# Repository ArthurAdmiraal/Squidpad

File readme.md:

# Squidpad
### About
The squidpad is a Slim Quality Uncostly Intuitive Drawing Pad. These are all the source files. This is an open project, which I'm documenting on [hackaday.io](https://hackaday.io/project/7153-squidpad).

### Repository structure
All design files go in the `Project` folder. Any files just made for documentation, such as a diagram in GeoGebra, can be found in the `Documentation` folder.

In both folders, the `Design files` folder contains source files. In the `Documentation` folder, any diagrams of pictures are just in the top-level folder. In the `Project` folder however, files generated using the design software, such as gerber files, can be found in the `Manifacturing` folder. People that just want to have a look at the board can find pdf's and OSHpark renders in the `Easily viewable` folder.

### License
All files in the `Project` folder are licensed under the [Creative Commons Attribution-NonCommercial-ShareAlike 4.0 International](http://creativecommons.org/licenses/by-nc-sa/4.0/) license. Everything in the `Documentation` folder can be used under the [Creative Commons Attribution-ShareAlike 4.0 International](http://creativecommons.org/licenses/by-sa/4.0/) license.

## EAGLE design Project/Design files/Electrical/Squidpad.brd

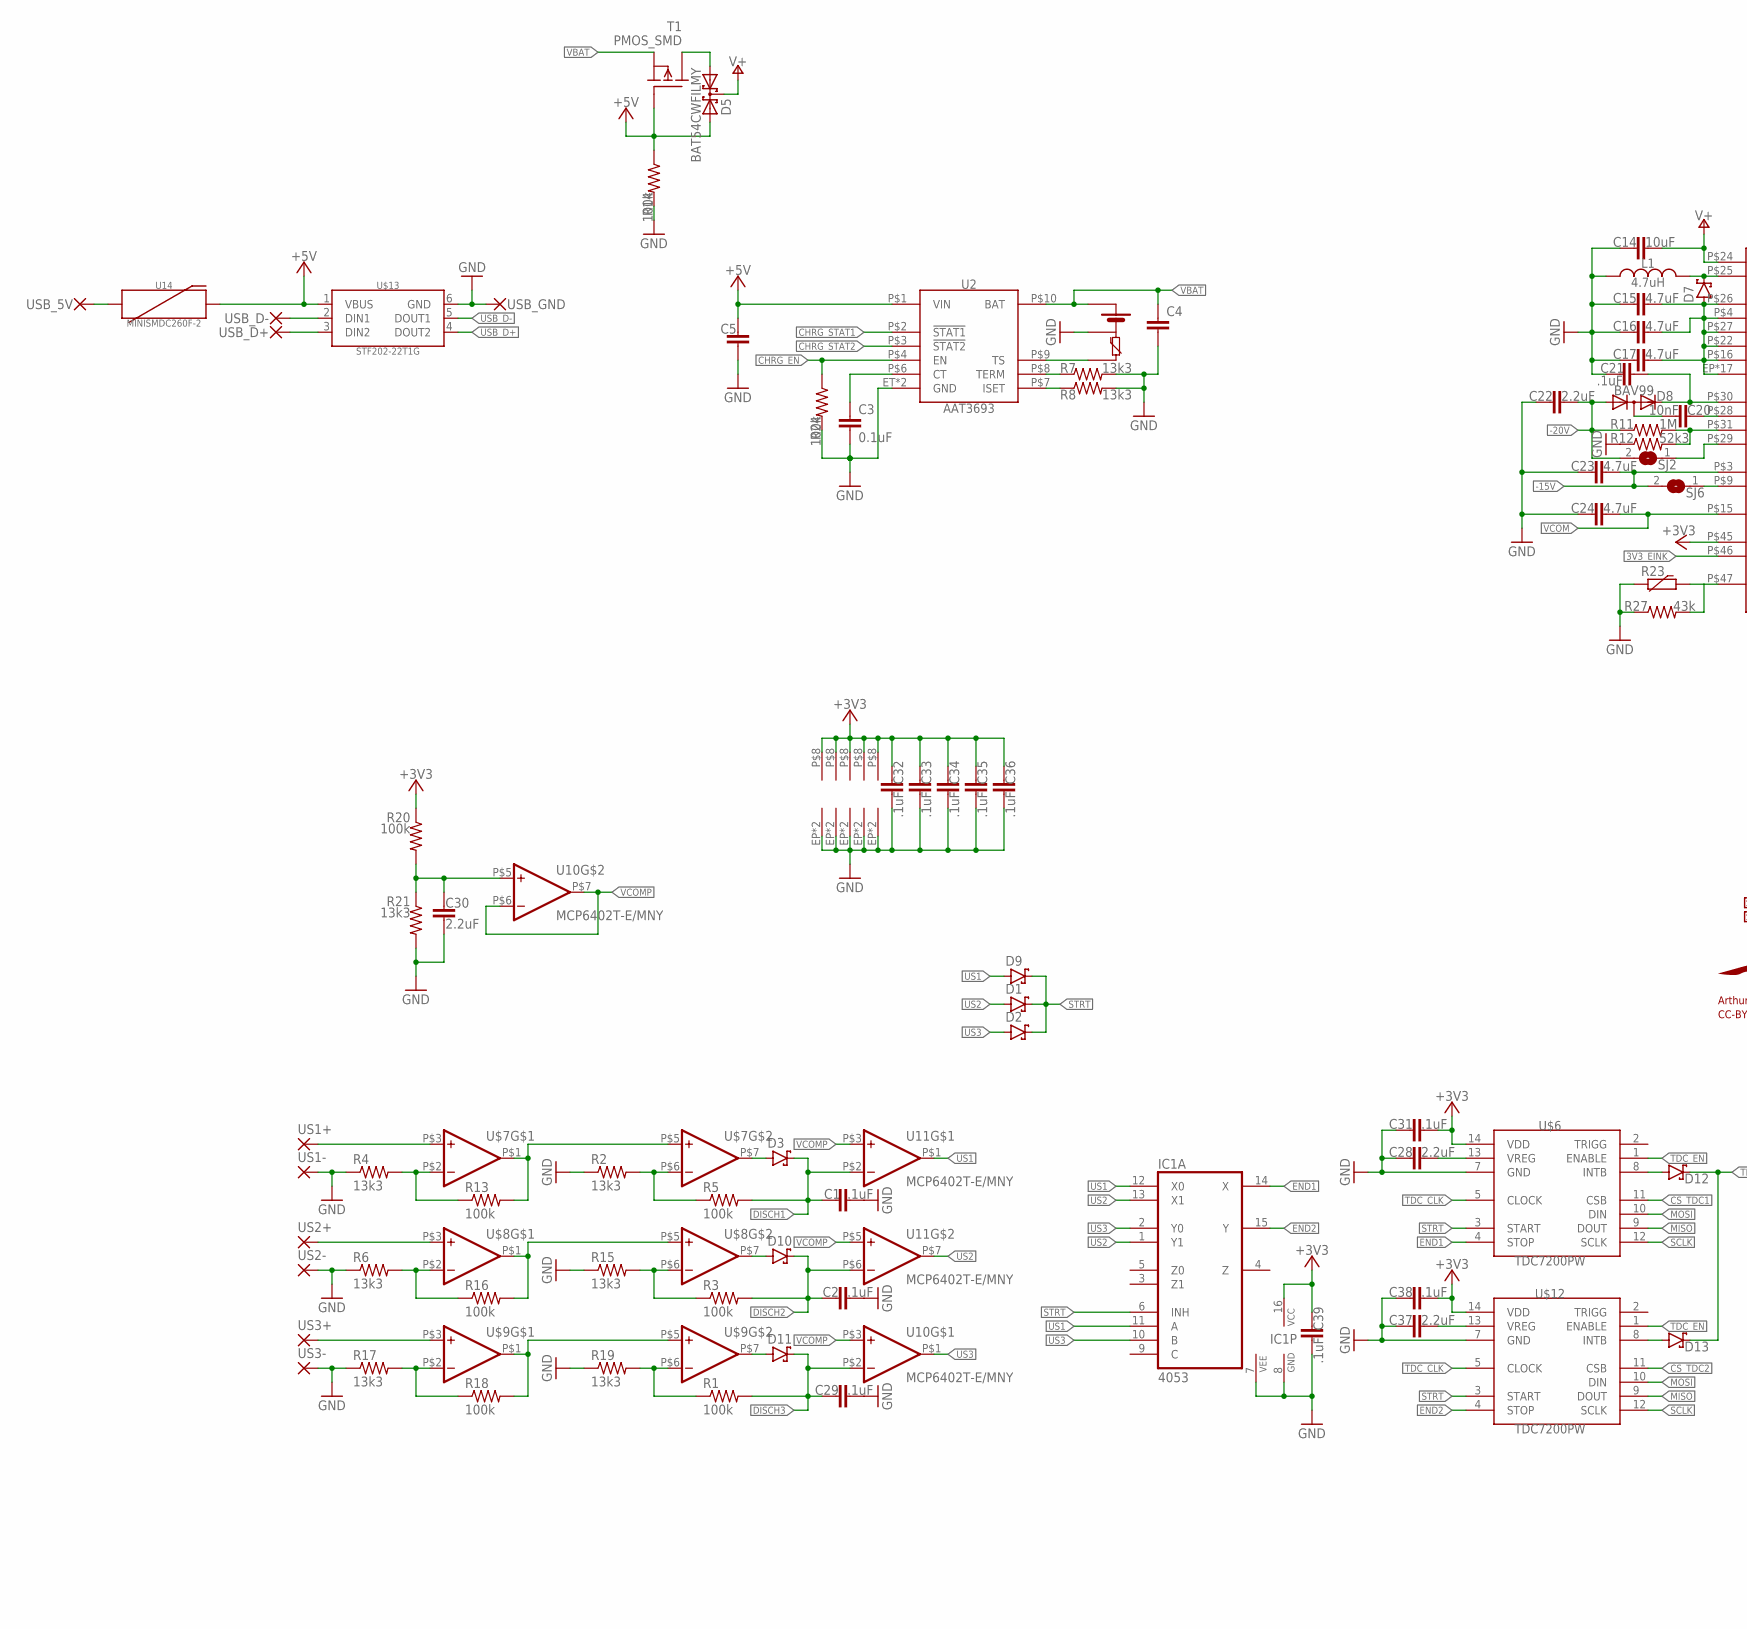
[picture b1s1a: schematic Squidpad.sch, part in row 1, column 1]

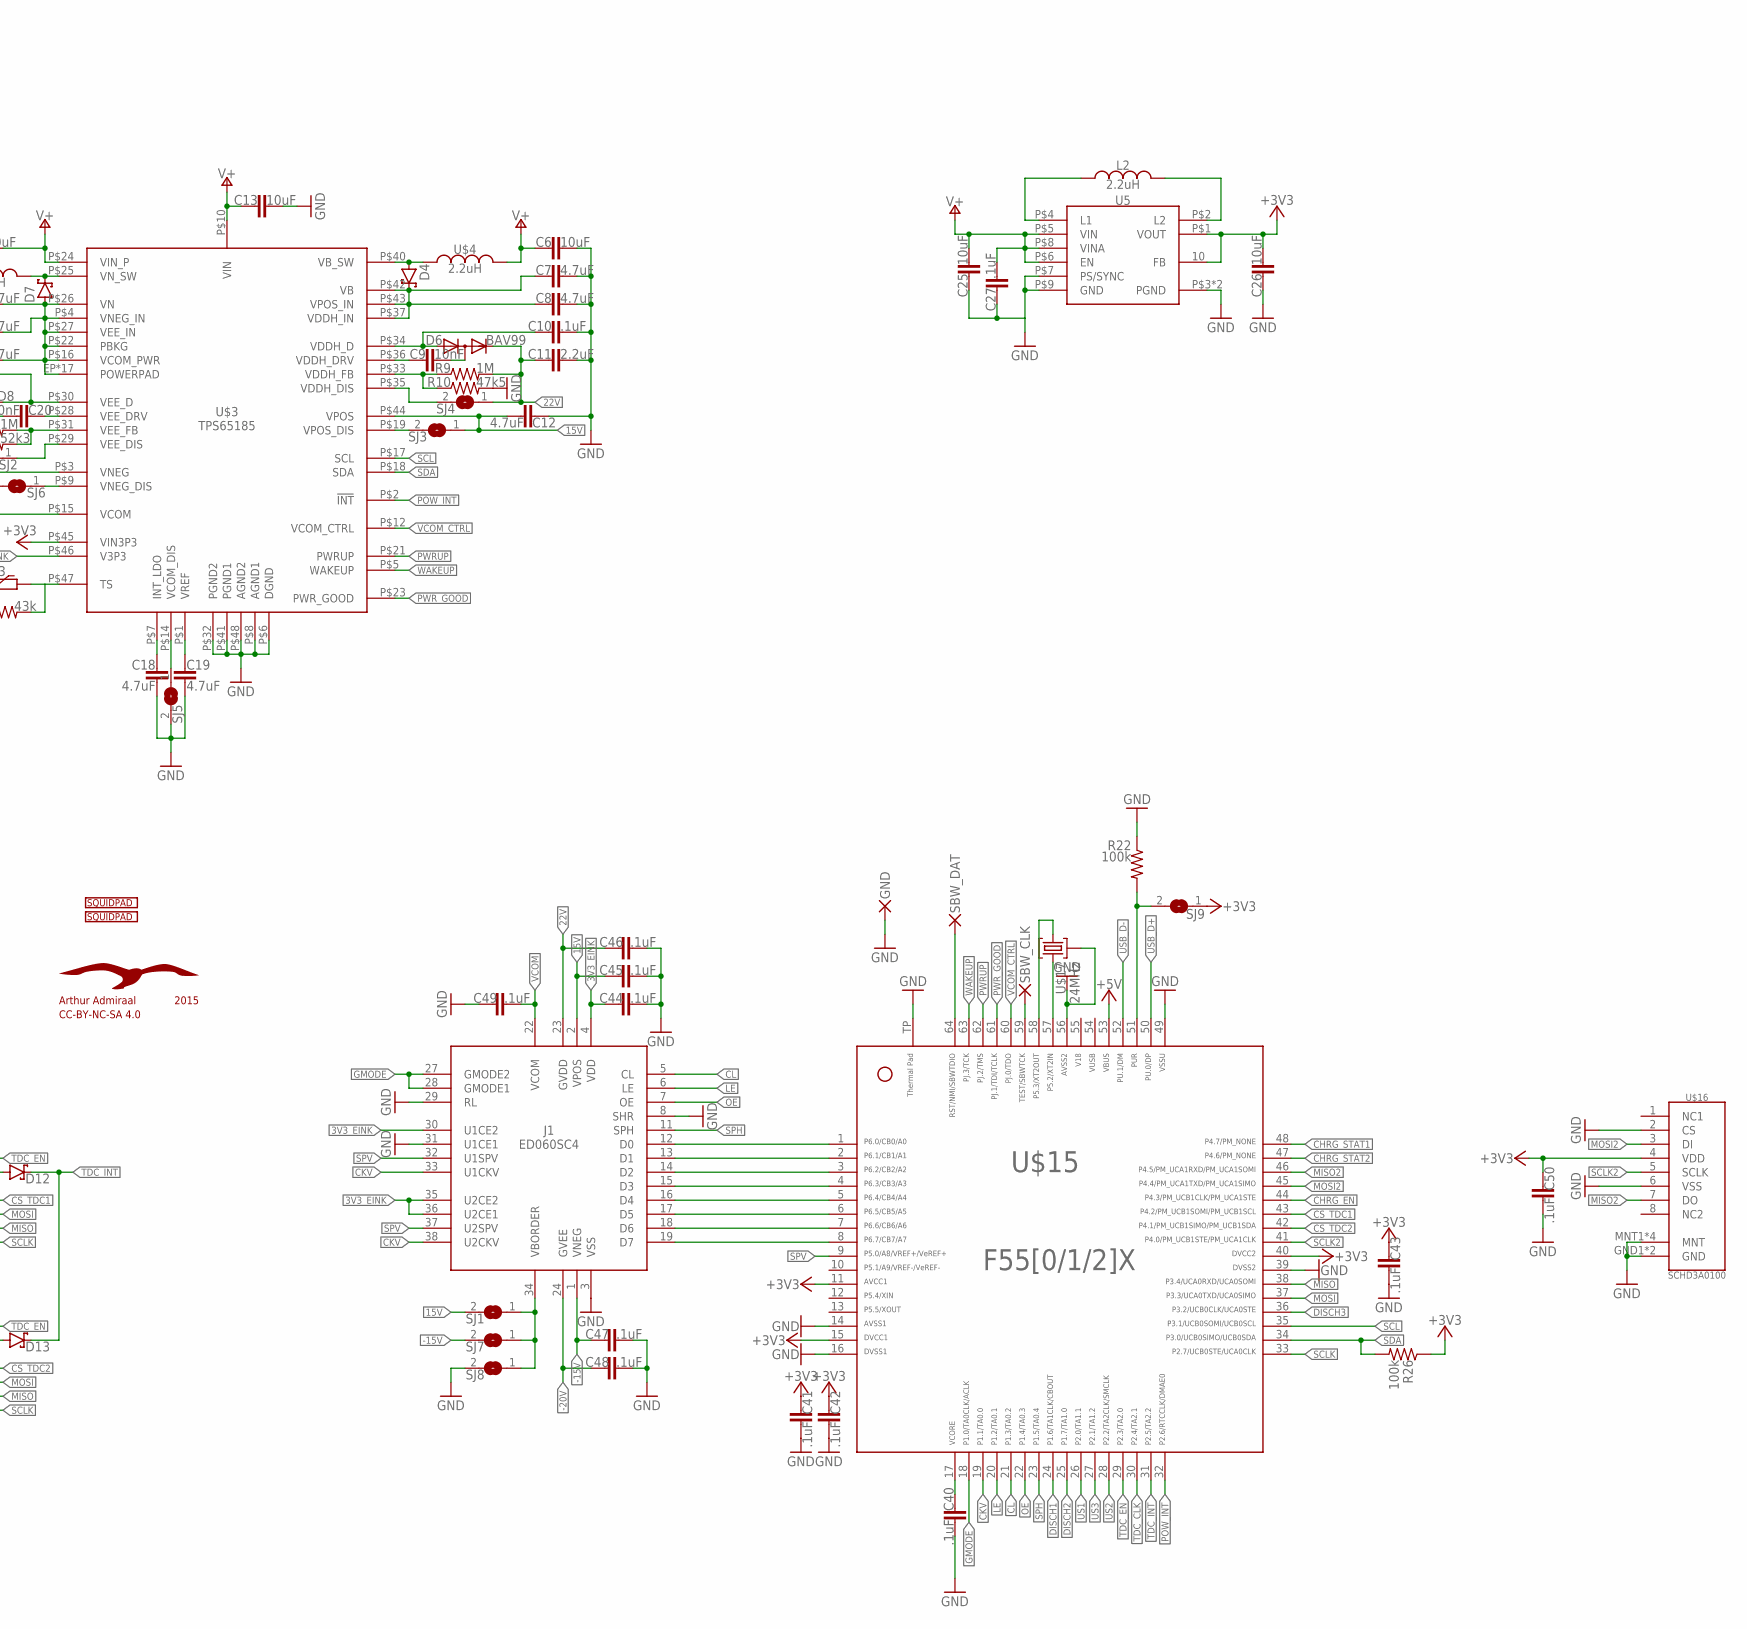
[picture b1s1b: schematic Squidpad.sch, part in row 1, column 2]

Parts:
C1, C2, C10, C21, C27, C29, C31, C32, C33, C34, C35, C36, C38, C39, C40, C41, C42, C43, C44, C45, C46, C47, C48, C49, C50: .1uF; C0805K
C3: 0.1uF; 0603-CAP
C4, C5: CAP0603-CAP; 0603-CAP
C6, C13, C14, C25, C26: 10uF; C0805K
C7, C8, C12, C15, C16, C17, C18, C19, C23, C24: 4.7uF; C0805K
C9, C20: 10nF; C0603K
C11, C22, C28, C30, C37: 2.2uF; C0603K
D1, D2, D3, D4, D7, D9, D10, D11, D12, D13: MBR130T3G; SOD123
D5: BAT54CWFILMY; SOT323
D6, D8: BAV99; SOT23
GND: SMD2; SMD1,27-2,54
IC1: 4053; TSSOP16
J1: ED060SC4; FH26-39S-0.3SHW(05)
L1: 4.7uH; LQH44P
L2: 2.2uH; NR4012
R1, R3, R5, R13, R14, R16, R18, R20, R22, R24, R26: 100k; R0603
R2, R4, R6, R15, R17, R19, R21: 13k3; R1206
R7, R8: 13k3; R0603
R9, R11: 1M; R0603
R10: 47k5; R0603
R12: 52k3; R0603
R23: R-EU_R0603; R0603
R27: 43k; R0603
SBW_CLK: SMD2; SMD1,27-2,54
SBW_DAT: SMD2; SMD1,27-2,54
SJ1, SJ2, SJ3, SJ4, SJ5, SJ6, SJ7, SJ8, SJ9: SJ
T1: PMOS_SMD; SOT323R_INFINEON
U2: AAT3693; TDFN14
U5: TPS63031; R-PWSON-N10
U10, U11: MCP6402T-E/MNY; TFDN8
U14: MINISMDC260F-2
U$1: IPOD_NANO_5_BATTERY
U$2: SQUIDPAD_LOGOSQUIDPAD_LOGO_SMALL; SQUIDPAD_LOGO_LOWPOLY_SMALL
U$3: TPS65185; VQFN48
U$4: 2.2uH; NR4012
U$5: SQUIDPAD_LOGOSQUIDPAD_LOGO; SQUIDPAD_LOGO_LOWPOLY
U$6, U$12: TDC7200PW; TSSOP14
U$7, U$8, U$9: MCP6402T-E/MNY; TFDN8
U$10: AALECTRONICS_SEAGULL
U$13: STF202-22T1G; SOT23-6
U$15: F55[0/1/2]X---RGC64; RGC64
U$16: SCHD3A0100
U$17: 24MHz; TSX-3225
US1+, US1-, US2+, US2-, US3+, US3-: SMD2; SMD1,27-2,54
USB_5V: SMD2; SMD1,27-2,54
USB_D+: SMD2; SMD1,27-2,54
USB_D-: SMD2; SMD1,27-2,54
USB_GND: SMD2; SMD1,27-2,54

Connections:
3V3: C6.1, C13.1, C14.2, C25.2, C27.2, D5.3 (C), U5.P$5 (VIN), U5.P$6 (EN), U5.P$8 (VINA), U$3.P$10 (VIN), U$3.P$24 (VIN_P), U$4.P$2
3V3_EINK: C44.1, J1.4 (VDD), J1.30 (U1CE2), J1.35 (U2CE2), J1.36 (U2CE1), U$3.P$46 (V3P3)
15V: C12.2, C45.1, J1.2 (VPOS), SJ1.2, SJ3.1, U$3.P$44 (VPOS)
22V: C11.1, C46.1, D6.2 (C), J1.23 (GVDD), R9.2, SJ4.1
54: U$15.54
55: U$15.55
+3V3: C26.2, C31.2, C32.1, C33.1, C34.1, C35.1, C36.1, C38.2, C39.1, C41.1, C42.1, C43.1, C50.1, IC1.16 (VCC), R20.1, R26.1, SJ9.1, U5.10 (FB), U5.P$1 (VOUT), U10.P$8 (V+), U11.P$8 (V+), U$3.P$45 (VIN3P3), U$6.14 (VDD), U$7.P$8 (V+), U$8.P$8 (V+), U$9.P$8 (V+), U$12.14 (VDD), U$15.11, U$15.15, U$15.40, U$16.4 (VDD)
+5V: C5.1, D5.2 (A2), R14.1, T1.1 (G), U2.P$1 (VIN), U14.P$2, U$13.1 (VBUS), U$15.53
-15V: C23.2, C47.1, J1.1 (VNEG), SJ6.2, SJ7.2, U$3.P$3 (VNEG)
-20V: C22.2, C48.1, D8.1 (A), J1.24 (GVEE), R11.1, SJ2.2
CHRG_EN: R24.1, U2.P$4 (EN), U$15.44
CHRG_STAT1: U2.P$2 (!STAT1), U$15.48
CHRG_STAT2: U2.P$3 (!STAT2), U$15.47
CKV: J1.33 (U1CKV), J1.38 (U2CKV), U$15.19
CL: J1.5 (CL), U$15.21
CS_TDC1: U$6.11 (CSB), U$15.43
CS_TDC2: U$12.11 (CSB), U$15.42
D0: J1.12 (D0), U$15.1
D1: J1.13 (D1), U$15.2
D2: J1.14 (D2), U$15.3
D3: J1.15 (D3), U$15.4
D4: J1.16 (D4), U$15.5
D5: J1.17 (D5), U$15.6
D6: J1.18 (D6), U$15.7
D7: J1.19 (D7), U$15.8
DISCH1: C1.1, D3.1 (C), R5.2, U11.P$2 (-IN), U$15.24
DISCH2: C2.1, D10.1 (C), R3.2, U11.P$6 (-IN), U$15.25
DISCH3: C29.1, D11.1 (C), R1.2, U10.P$2 (-IN), U$15.36
END1: IC1.14 (X), U$6.4 (STOP)
END2: IC1.15 (Y), U$12.4 (STOP)
GMODE: J1.27 (GMODE2), J1.28 (GMODE1), U$15.18
GND: C1.2, C2.2, C3.2, C4.2, C5.2, C6.2, C7.2, C8.2, C10.2, C11.2, C12.1, C13.2, C14.1, C15.1, C16.1, C17.1, C18.1, C19.1, C21.1, C22.1, C23.1, C24.1, C25.1, C26.1, C27.1, C28.1, C29.2, C30.2, C31.1, C32.2, C33.2, C34.2, C35.2, C36.2, C37.1, C38.1, C39.2, C40.2, C41.2, C42.2, C43.2, C44.2, C45.2, C46.2, C47.2, C48.2, C49.1, C50.2, GND.1, IC1.7 (VEE), IC1.8 (GND), J1.3 (VSS), J1.8 (SHR), J1.29 (RL), J1.31 (U1CE1), L1.P$1, R2.1, R4.1, R6.1, R7.2, R8.2, R10.2, R12.1, R14.2, R15.1, R17.1, R19.1, R21.2, R22.1, R23.1, R24.2, R27.1, SJ5.2, SJ8.2, U2.ET (GND), U2.P$5 (GND), U5.P$3 (PGND), U5.P$7 (PS/SYNC), U5.P$9 (GND), U5.POWERPAD (PGND), U10.EP (V-), U10.P$4 (V-), U11.EP (V-), U11.P$4 (V-), U$1.P- (BATTERY-), U$3.P$6 (DGND), U$3.P$8 (AGND1), U$3.P$32 (PGND2), U$3.P$41 (PGND1), U$3.P$48 (AGND2), U$6.7 (GND), U$7.EP (V-), U$7.P$4 (V-), U$8.EP (V-), U$8.P$4 (V-), U$9.EP (V-), U$9.P$4 (V-), U$12.7 (GND), U$13.6 (GND), U$15.14, U$15.16, U$15.39, U$15.49, U$15.56, U$15.TP, U$16.2 (CS), U$16.6 (VSS), U$16.GND1 (GND), U$16.GND2 (GND), U$16.MNT1 (MNT), U$16.MNT2 (MNT), U$16.MNT3 (MNT), U$16.MNT4 (MNT), U$17.2, U$17.3 (2), US1-.1, US2-.1, US3-.1, USB_GND.1
LE: J1.6 (LE), U$15.20
MISO: U$6.9 (DOUT), U$12.9 (DOUT), U$15.38
MISO2: U$15.46, U$16.7 (DO)
MOSI: U$6.10 (DIN), U$12.10 (DIN), U$15.37
MOSI2: U$15.45, U$16.3 (DI)
unnamed: U$7.P$3 (+IN), US1+.1
unnamed: R2.2, R5.1, U$7.P$6 (-IN)
unnamed: D12.2 (A), U$6.8 (INTB)
unnamed: U$8.P$3 (+IN), US2+.1
unnamed: R6.2, R16.1, U$8.P$2 (-IN)
unnamed: R16.2, U$8.P$1 (OUT), U$8.P$5 (+IN)
unnamed: D4.2 (A), U$3.P$40 (VB_SW), U$4.P$1
unnamed: U2.P$9 (TS), U$1.TH (TEMP)
unnamed: U$13.3 (DIN2), USB_D+.1
unnamed: U$13.2 (DIN1), USB_D-.1
unnamed: U$15.57, U$17.4 (3)
unnamed: R7.1, U2.P$8 (TERM)
unnamed: R8.1, U2.P$7 (ISET)
unnamed: C7.1, C8.1, D4.1 (C), U$3.P$37 (VDDH_IN), U$3.P$42 (VB), U$3.P$43 (VPOS_IN)
unnamed: D3.2 (A), U$7.P$7 (OUT)
unnamed: D13.2 (A), U$12.8 (INTB)
unnamed: C3.1, U2.P$6 (CT)
unnamed: C10.1, D6.1 (A), U$3.P$34 (VDDH_D)
unnamed: D5.1 (A1), T1.3 (D)
unnamed: C9.1, U$3.P$36 (VDDH_DRV)
unnamed: C9.2, D6.3 (AC)
unnamed: R9.1, R10.1, U$3.P$33 (VDDH_FB)
unnamed: C20.2, D8.3 (AC)
unnamed: D7.1 (C), L1.P$2, U$3.P$25 (VN_SW)
unnamed: C15.2, C16.2, C17.2, D7.2 (A), U$3.EP (POWERPAD), U$3.EP1 (POWERPAD), U$3.EP2 (POWERPAD), U$3.EP3 (POWERPAD), U$3.EP4 (POWERPAD), U$3.EP5 (POWERPAD), U$3.EP6 (POWERPAD), U$3.EP7 (POWERPAD), U$3.EP8 (POWERPAD), U$3.EP9 (POWERPAD), U$3.EP10 (POWERPAD), U$3.EP11 (POWERPAD), U$3.EP12 (POWERPAD), U$3.EP13 (POWERPAD), U$3.EP14 (POWERPAD), U$3.EP15 (POWERPAD), U$3.EP16 (POWERPAD), U$3.P$4 (VNEG_IN), U$3.P$16 (VCOM_PWR), U$3.P$22 (PBKG), U$3.P$26 (VN), U$3.P$27 (VEE_IN)
unnamed: C18.2, U$3.P$7 (INT_LDO)
unnamed: C19.2, U$3.P$1 (VREF)
unnamed: C21.2, D8.2 (C), U$3.P$30 (VEE_D)
unnamed: SJ6.1, U$3.P$9 (VNEG_DIS)
unnamed: L2.P$1, U5.P$4 (L1)
unnamed: C20.1, U$3.P$28 (VEE_DRV)
unnamed: R11.2, R12.2, U$3.P$31 (VEE_FB)
unnamed: SJ2.1, U$3.P$29 (VEE_DIS)
unnamed: SJ3.2, U$3.P$19 (VPOS_DIS)
unnamed: SJ4.2, U$3.P$35 (VDDH_DIS)
unnamed: SJ5.1, U$3.P$14 (VCOM_DIS)
unnamed: L2.P$2, U5.P$2 (L2)
unnamed: C28.2, U$6.13 (VREG)
unnamed: R4.2, R13.1, U$7.P$2 (-IN)
unnamed: R13.2, U$7.P$1 (OUT), U$7.P$5 (+IN)
unnamed: R3.1, R15.2, U$8.P$6 (-IN)
unnamed: U14.P$1, USB_5V.1
unnamed: U$9.P$3 (+IN), US3+.1
unnamed: R17.2, R18.1, U$9.P$2 (-IN)
unnamed: R18.2, U$9.P$1 (OUT), U$9.P$5 (+IN)
unnamed: R1.1, R19.2, U$9.P$6 (-IN)
unnamed: D10.2 (A), U$8.P$7 (OUT)
unnamed: D11.2 (A), U$9.P$7 (OUT)
unnamed: C37.2, U$12.13 (VREG)
unnamed: J1.34 (VBORDER), SJ1.1, SJ7.1, SJ8.1
unnamed: SBW_DAT.1, U$15.64
unnamed: SBW_CLK.1, U$15.59
unnamed: C40.1, U$15.17
unnamed: R22.2, SJ9.2, U$15.51
unnamed: U$15.58, U$17.1
unnamed: R23.2, R27.2, U$3.P$47 (TS)
OE: J1.7 (OE), U$15.22
POW_INT: U$3.P$2 (!INT), U$15.32
PWRUP: U$3.P$21 (PWRUP), U$15.62
PWR_GOOD: U$3.P$23 (PWR_GOOD), U$15.61
SCL: U$3.P$17 (SCL), U$15.35
SCLK: U$6.12 (SCLK), U$12.12 (SCLK), U$15.33
SCLK2: U$15.41, U$16.5 (SCLK)
SDA: R26.2, U$3.P$18 (SDA), U$15.34
SPH: J1.11 (SPH), U$15.23
SPV: J1.32 (U1SPV), J1.37 (U2SPV), U$15.9
STRT: D1.1 (C), D2.1 (C), D9.1 (C), IC1.6 (INH), U$6.3 (START), U$12.3 (START)
TDC_CLK: U$6.5 (CLOCK), U$12.5 (CLOCK), U$15.30
TDC_EN: U$6.1 (ENABLE), U$12.1 (ENABLE), U$15.29
TDC_INT: D12.1 (C), D13.1 (C), U$15.31
US1: D9.2 (A), IC1.11 (A), IC1.12 (X0), U11.P$1 (OUT), U$15.26
US2: D1.2 (A), IC1.1 (Y1), IC1.13 (X1), U11.P$7 (OUT), U$15.28
US3: D2.2 (A), IC1.2 (Y0), IC1.10 (B), U10.P$1 (OUT), U$15.27
USB_D+: U$13.4 (DOUT2), U$15.50
USB_D-: U$13.5 (DOUT1), U$15.52
VBAT: C4.1, T1.2 (S), U2.P$10 (BAT), U$1.P+ (BATTERY+)
VCOM: C24.2, C49.2, J1.22 (VCOM), U$3.P$15 (VCOM)
VCOMP: U10.P$3 (+IN), U10.P$6 (-IN), U10.P$7 (OUT), U11.P$3 (+IN), U11.P$5 (+IN)
VCOMP_BEFORE: C30.1, R20.2, R21.1, U10.P$5 (+IN)
VCOM_CTRL: U$3.P$12 (VCOM_CTRL), U$15.60
WAKEUP: U$3.P$5 (WAKEUP), U$15.63

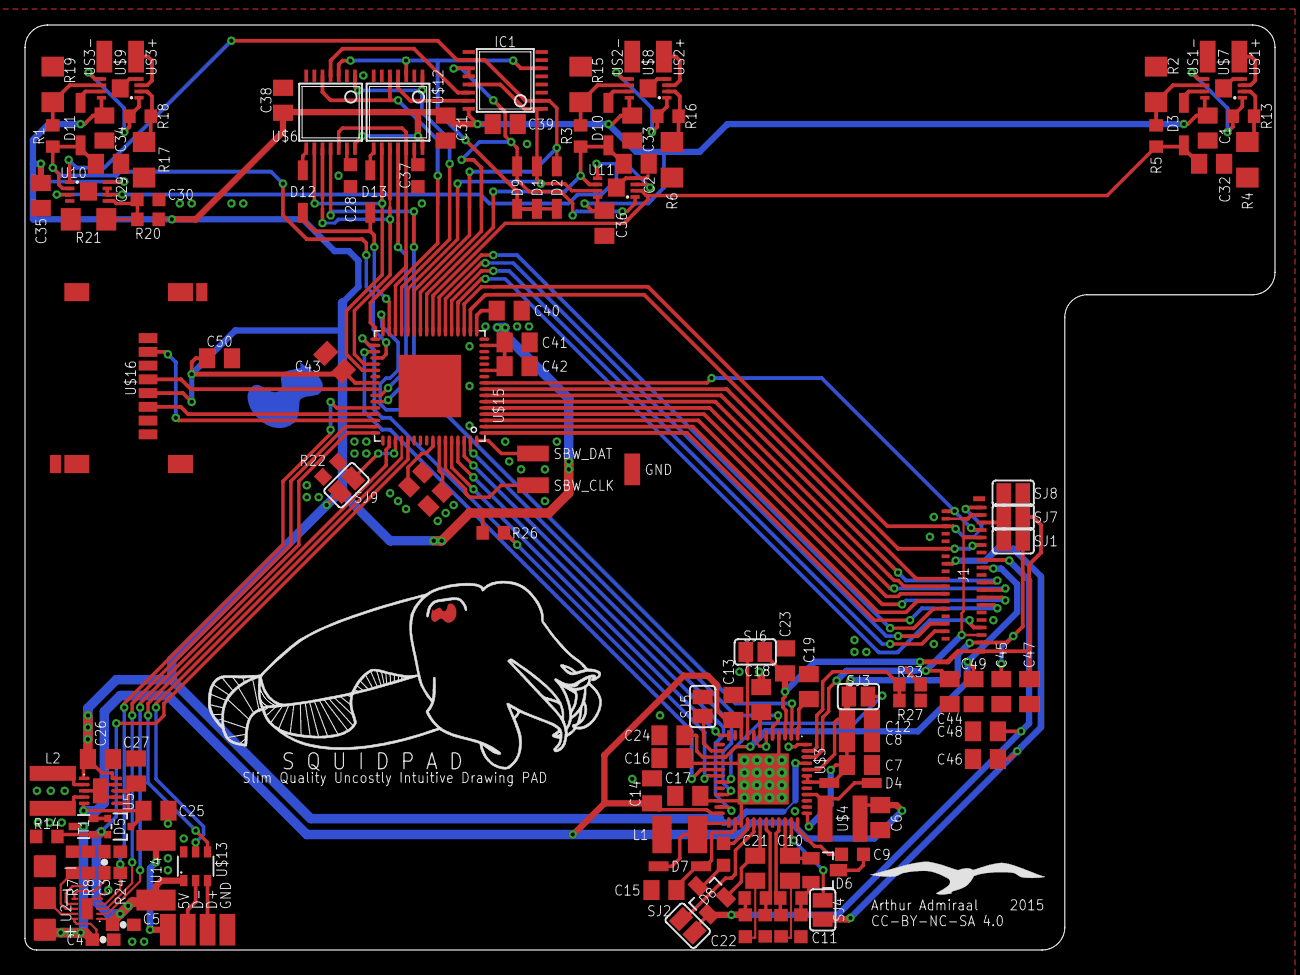
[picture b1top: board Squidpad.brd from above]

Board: 2 copper layers, 100.0 x 74.0 mm, 136 parts (1 on the bottom side), 116 nets.

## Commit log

2015-08-16 Adds system diagram

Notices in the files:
parts and their libraries:
SparkFun-Capacitors: Licensing: Creative Commons ShareAlike 4.0 International - https://creativecommons.org/licenses/by-sa/4.0
aalectronics: CC-BY-NC-SA 4.0
